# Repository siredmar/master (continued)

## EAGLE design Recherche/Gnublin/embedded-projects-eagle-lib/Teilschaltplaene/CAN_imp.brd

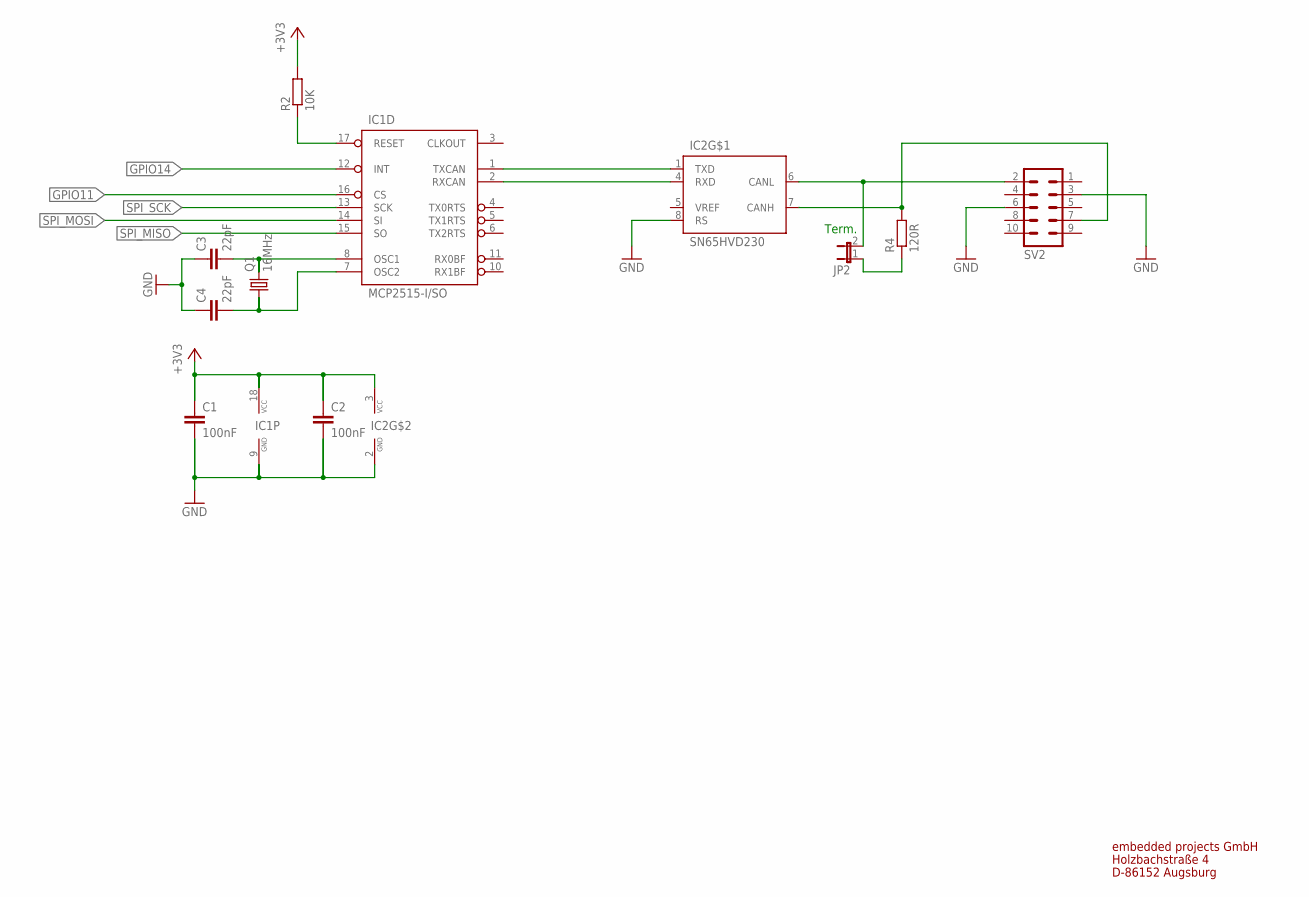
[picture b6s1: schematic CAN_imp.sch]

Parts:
C1, C2: 100nF; C0805
C3, C4: 22pF; C0805
IC1: MCP2515-I/SO; SO-18W; FARNELL 1292239
IC2: SN65HVD230; SO08; FARNELL 1103105
JP2: JP1E; JP1
Q1: 16MHz; HC49UP
R2: 10K; R0805
R4: 120R; R0805
SV2: ML10

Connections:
+3V3: C1.1, C2.1, IC1.18 (VCC), IC2.3 (VCC), R2.2
CANH: IC2.7 (CANH), R4.2, SV2.7
CANL: IC2.6 (CANL), JP2.2, SV2.2
GND: C1.2, C2.2, C3.1, C4.1, IC1.9 (GND), IC2.2 (GND), IC2.8 (RS), SV2.3, SV2.6
GPIO11: IC1.16 (CS)
GPIO14: IC1.12 (INT)
unnamed: C3.2, IC1.8 (OSC1), Q1.2
unnamed: C4.2, IC1.7 (OSC2), Q1.1
unnamed: IC1.1 (TXCAN), IC2.1 (TXD)
unnamed: IC1.2 (RXCAN), IC2.4 (RXD)
unnamed: IC1.17 (RESET), R2.1
unnamed: JP2.1, R4.1
SPI_MISO: IC1.15 (SO)
SPI_MOSI: IC1.14 (SI)
SPI_SCK: IC1.13 (SCK)

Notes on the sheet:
Term.
embedded projects GmbH
Holzbachstraße 4
D-86152 Augsburg

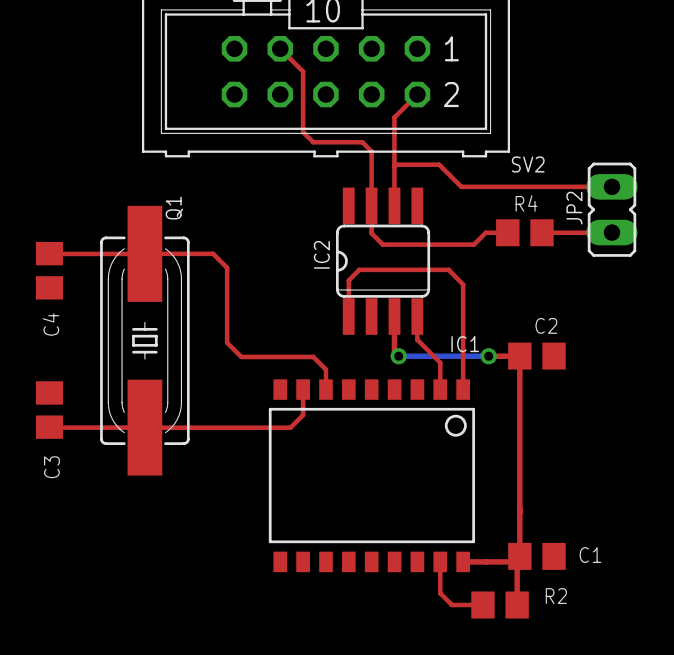
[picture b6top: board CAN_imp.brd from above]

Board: 2 copper layers, 11 parts (0 on the bottom side), 10 nets.

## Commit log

2014-03-02 uploaded current workset 02.03.2014
2014-03-02 deleted linux-2.6.28.2
2014-03-02 work in userspace driver
2014-03-02 cleared object files
2014-03-02 edited userspace driver
2014-03-03 test commit from different computer
2014-03-03 end of Workday - 03.03.2014
2014-03-03 edited Readme
2014-03-12 APEX display initializes
2014-03-12 Userspace Driver can read out signature
2014-03-13 end of workday 13.03.2014 - compared DIP with EXT - commands are the same - maybe EMV problem?
2014-03-14 end of workday 14.03.2014 - software works correctly, hardware works correctly - display can not work with > 22 MHz bus frequency
2014-03-15 SSD1289 working user space driver - this is the wanted proof that the SSD1963 display is junk
2014-03-17 added Displays in Bestellung
2014-03-19 first version of order list
2014-03-20 added first version of eagle lbr
2014-03-20 updated eagle lbr
2014-03-20 end of workday 20.03.2014
2014-03-21 end of workday 21.03.2014
2014-03-22 end of workday 22.03.2014
2014-03-24 commit mid 24.03.2014
2014-03-24 end of workday 24.03.2014
2014-03-25 uploaded finished schematic and layout
2014-03-26 end of workday 26.03.2014
2014-03-27 updated V4 of layout
2014-03-27 updated version of V4
2014-03-29 uploaded texworks tgz for slackware
2014-03-29 added Masterarbeit LaTeX template
2014-03-29 Masterarbeit Kap.1 work
2014-03-29 updated Bestellliste
2014-03-29 updated schematic and layout
2014-03-29 added working directory of embedded software
2014-03-30 end of workday 30.03.2014
2014-03-31 end of workday 31.03.2014
2014-04-01 bevor review
2014-04-01 end of workday 01.04.2014
2014-04-02 schematic and layout adapted
2014-04-02 finished GUI, V5 of layout - end of workday 02.04.2014
2014-04-03 end of workday 03.04.2014 - BIG TODO: edid_writer RS232 Code
2014-04-07 end of workday 07.04.2014 - found RS232 bug
2014-04-08 end of workday 08.04.2013 - checksum working - rs232 dropout still present
2014-04-09 edid_writer working
2014-04-09 updated edid_writer
2014-04-09 end of workday 09.04.2014 - edid_writer beta state
2014-04-10 error check in embedded software added
2014-04-10 writing and reading to eeprom works - checksum needs to be fixed
2014-04-11 edid Writer V1 - ported software to ATMega328p
2014-04-14 Inhaltsverzeichnis in Doku hinzugefuegt
2014-04-14 Inhaltsverzeichnis modifiziert
2014-04-14 end of workday 14.04.2014
2014-04-15 end of workday 15.04.2014
2014-04-17 end of workday 16.04.2014
2014-04-17 restructuring of complete worktree
2014-04-17 updated Inhaltsverzeichnis
2014-04-17 end of workday 17.04.2014
2014-04-23 removed whitespaces in directory names
2014-04-23 MD050SD working
2014-04-28 updated eagle library and review document for review
2014-04-28 reviewd lbr, changd schematics to V7
2014-04-28 updated simulations
2014-04-28 Bestellliste updated
2014-04-29 MD050SD framebuffer driver working
2014-04-30 changed SSD1289 driver for line update, thoughts about image converter for framebuffer testing
2014-05-01 finished img2raw converter tool
2014-05-02 end of workday 02.05.2014 - ssd1289 seems broken?
2014-05-05 end of workday 06.05.2014 - ssd1963 pll initialization in bootloader won't work - memcpy in framebuffer driver not faster than own update routine
2014-05-05 updated TEIL_A schematics and layout; git commit -am 'updated TEIL_A schematics and layout
2014-05-06 TEIL_B: reviewed schematic and layout
2014-05-06 cleared git error
2014-05-06 TEIL_A: modified schematics
2014-05-06 todo list
2014-05-06 added sainsmart 3.2 files
2014-05-08 end of workday 08.05.2014 - ssd1298 framebuffer driver kind of working. Needs to be fixed
2014-05-13 updated schematics and layout to V9
2014-05-13 updated img2raw
2014-05-13 end of workday 13.05.2014 - added boot logo in bootloader
2014-05-13 created instructions for software, vanilla sources and patches
2014-05-13 updated docu
2014-05-13 final version of docu
2014-05-20 renamed TEIL_A schematics
2014-05-20 converted LaTeX file to UTF8
2014-05-20 end of workday 20.05.2014
2014-05-22 end of workday 22.05.2014
2014-05-28 end of workday 28.05.2014
2014-06-03 end of workday - inbetriebnahme: 5V Teil funktioniert mit AVR, FTDI und EEPROM, USB D- und D+ vertauscht, R13 mit 0R getauscht, HDMI Stecker muss gekreuzt werden
2014-07-28 updated Documenation
2014-07-29 end of workday 29.07.2014
2014-07-31 end of workday 31.07.2014
2014-08-04 chapter bootloader kind of finished
2014-08-05 zwischenstand 05.08.2014
2014-08-05 zwischenstand 2 05.08.2014
2014-08-05 end of workday 05.08.2014
2014-08-06 framebuffer driver finished
2014-08-06 code cleanup no. 1
2014-08-06 zwischenstand 06.08.2014
2014-08-06 end of workday 06.08.2014
2014-08-07 end of workday 07.08.2014
2014-08-12 Teil A finished
2014-08-12 pdf build of teil a finished
2014-08-13 end of workday 13.08.2014
2014-08-20 end of workday 19.08.2014
2014-08-20 end of workday 20.08.2014
2014-08-21 zwischenstand 21.08.2014
2014-08-21 end of workday 21.08.2014
2014-08-22 end of workday 22.08.2014
2014-08-25 end of workday 25.08.2014 - kapitel 4 fertig
2014-08-26 zwischenstand 26.08.2014 - known bugs fertig
2014-08-26 end of workday 26.08.2014
2014-09-01 korrektur teil 1 - end of workday 01.09.2014
2014-09-02 Fertig zum Probelesen
2014-09-04 Korrektur Mama eingearbeitet
2014-09-09 Korrektur Simon eingearbeitet
2014-09-09 Korrektur Mirjam eingearbeitet
2014-09-15 Final Version V1 of Masterarbeit.pdf
2014-09-16 It's done when it's done. Well, it's done.
2014-09-16 Finished files reviewd
